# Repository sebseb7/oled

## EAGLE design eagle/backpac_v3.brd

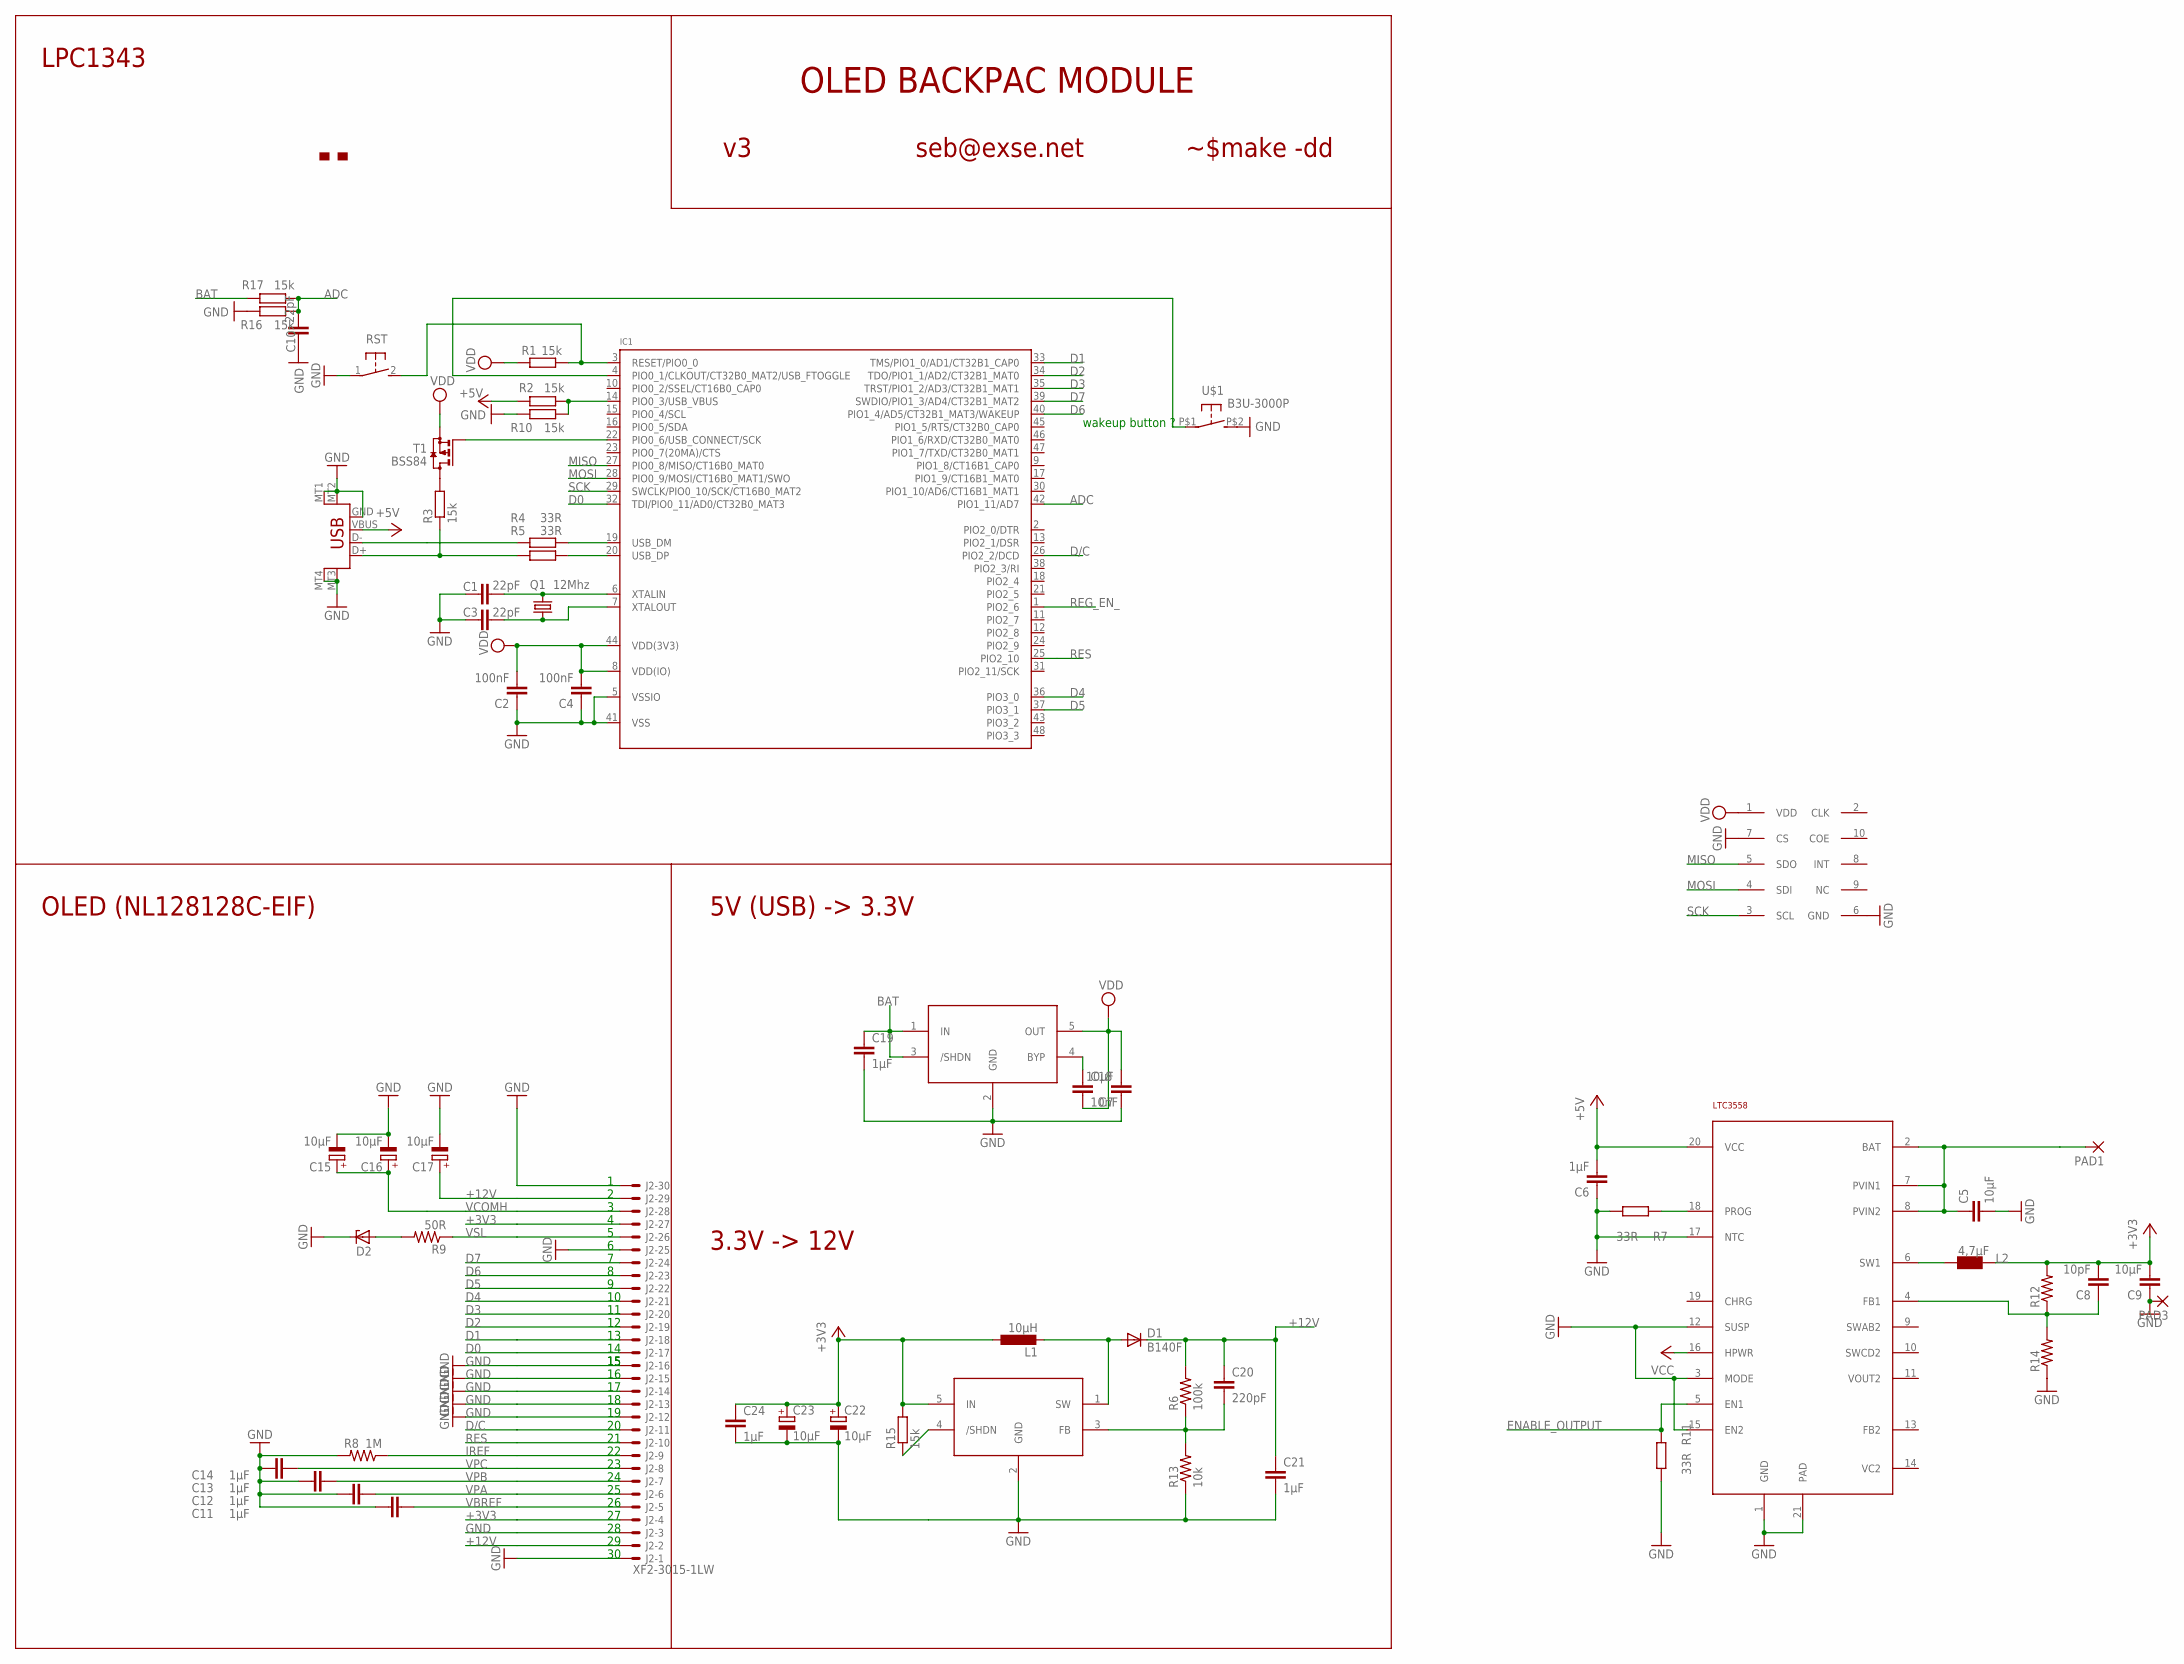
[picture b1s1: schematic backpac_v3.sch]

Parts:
C1, C3, C10: 22pF; C0402
C2, C4: 100nF; C0402
C5, C7, C9: 10µF; 0805
C6, C11, C12, C13, C14, C19, C21, C24: 1µF; 0805
C8: 10pF; 0805
C15, C16, C17, C22, C23: 10µF; SMC_A
C18: 10nF; 0402-CAP
C20: 220pF; 0805
D1: B140F; DO214AC
D2: ZENER-DIODESOT23; SOT23
IC1: LPC1343_QFP; LQFP48
IC2: LTC3558; UD-QFN20
IC3: LT1761; SOT23-5L
IC4: LM27313; SOT23-5L
IC5: RV-2123-C2
J2: XF2-3015-1LW; XF2H-3015-1LW
L1: 10µH; L1812
L2: 4,7µF; VLF4012A; PART VLF4012A
PAD1, PAD3: SMD2; SMD1,27-2,54
Q1: 12Mhz; MT
R1, R2, R3, R10, R15, R16, R17: 15k; R0402
R4, R5, R7, R11: 33R; R0402
R6: 100k; 0805
R8: 1M; 0805
R9: 50R; 0805
R12, R14: RESISTOR0805-RES; 0805
R13: 10k; 0805
RST: SWITCH_MCTAEF
T1: BSS84; SOT23
U$1: B3U-3000P
U$3: MAKE-DD_LOGO'REGULAR'; MAKE-DD_LOGO
X1: USB-MICROB

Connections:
+3V3: C8.2, C9.2, C22.+, C23.+, C24.1, IC4.5 (IN), J2.4 (MS), J2.27 (MS), L1.1, L2.P$4 (2), R12.2, R15.2
+5V: C6.2, IC2.20 (VCC), R2.2, X1.VBUS
+12V: C17.+, C20.1, C21.1, D1.C, J2.2 (MS), J2.29 (MS), R6.2
ADC: C10.2, IC1.42 (PIO1_11/AD7), R16.1, R17.1
BAT: C5.1, C19.1, IC2.2 (BAT), IC2.7 (PVIN1), IC2.8 (PVIN2), IC3.1 (IN), IC3.3 (/SHDN), PAD1.1, R17.2
D0: IC1.32 (TDI/PIO0_11/AD0/CT32B0_MAT3), J2.17 (MS)
D1: IC1.33 (TMS/PIO1_0/AD1/CT32B1_CAP0), J2.18 (MS)
D2: IC1.34 (TDO/PIO1_1/AD2/CT32B1_MAT0), J2.19 (MS)
D3: IC1.35 (TRST/PIO1_2/AD3/CT32B1_MAT1), J2.20 (MS)
D4: IC1.36 (PIO3_0), J2.21 (MS)
D5: IC1.37 (PIO3_1), J2.22 (MS)
D6: IC1.40 (PIO1_4/AD5/CT32B1_MAT3/WAKEUP), J2.23 (MS)
D7: IC1.39 (SWDIO/PIO1_3/AD4/CT32B1_MAT2), J2.24 (MS)
D/C: IC1.26 (PIO2_2/DCD), J2.11 (MS)
ENABLE_OUTPUT: IC2.5 (EN1), R11.2
GND: C1.1, C2.1, C3.1, C4.1, C5.2, C6.1, C7.1, C9.1, C10.1, C11.1, C12.1, C13.1, C14.1, C15.-, C16.-, C17.-, C19.2, C21.2, C22.-, C23.-, C24.2, D2.3 (C), IC1.5 (VSSIO), IC1.41 (VSS), IC2.1 (GND), IC2.3 (MODE), IC2.12 (SUSP), IC2.15 (EN2), IC2.17 (NTC), IC2.21 (PAD), IC3.2 (GND), IC4.2 (GND), IC5.6 (GND), IC5.7 (CS), J2.1 (MSV), J2.3 (MS), J2.12 (MS), J2.13 (MS), J2.14 (MS), J2.15 (MS), J2.16 (MS), J2.25 (MS), J2.30 (MS), PAD3.1, R7.1, R8.2, R10.2, R11.1, R13.1, R14.1, R16.2, RST.1, U$1.P$2 (2), X1.GND, X1.MT1 (GND), X1.MT2 (GND), X1.MT3 (GND), X1.MT4 (GND)
IREF: J2.9 (MS), R8.1
MISO: IC1.27 (PIO0_8/MISO/CT16B0_MAT0), IC5.5 (SDO)
MOSI: IC1.28 (PIO0_9/MOSI/CT16B0_MAT1/SWO), IC5.4 (SDI)
unnamed: IC2.18 (PROG), R7.2
unnamed: D2.1 (A), R9.2
unnamed: C3.2, IC1.7 (XTALOUT), Q1.1
unnamed: C1.2, IC1.6 (XTALIN), Q1.3 (2)
unnamed: D1.A, IC4.1 (SW), L1.2
unnamed: C20.2, IC4.3 (FB), R6.1, R13.2
unnamed: IC1.3 (RESET/PIO0_0), R1.1, RST.2
unnamed: R3.2, T1.3 (D)
unnamed: IC1.22 (PIO0_6/USB_CONNECT/SCK), T1.1 (G)
unnamed: R3.1, R5.2, X1.D+
unnamed: R4.2, X1.D-
unnamed: IC1.14 (PIO0_3/USB_VBUS), R2.1, R10.1
unnamed: C8.1, IC2.4 (FB1), R12.1, R14.2
unnamed: IC1.19 (USB_DM), R4.1
unnamed: IC2.6 (SW1), L2.P$3 (1)
unnamed: IC1.4 (PIO0_1/CLKOUT/CT32B0_MAT2/USB_FTOGGLE), U$1.P$1 (1)
unnamed: IC1.20 (USB_DP), R5.1
unnamed: C18.1, IC3.4 (BYP)
REG_EN_: IC1.1 (PIO2_6), IC4.4 (/SHDN), R15.1
RES: IC1.25 (PIO2_10), J2.10 (MS)
SCK: IC1.29 (SWCLK/PIO0_10/SCK/CT16B0_MAT2), IC5.3 (SCL)
VBREF: C11.2, J2.5 (MS)
VCC: IC2.16 (HPWR)
VCOMH: C15.+, C16.+, J2.28 (MS)
VDD: C2.2, C4.2, C7.2, C18.2, IC1.8 (VDD(IO)), IC1.44 (VDD(3V3)), IC3.5 (OUT), IC5.1 (VDD), R1.2, T1.2 (S)
VPA: C12.2, J2.6 (MS)
VPB: C13.2, J2.7 (MS)
VPC: C14.2, J2.8 (MS)
VSL: J2.26 (MS), R9.1

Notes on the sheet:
wakeup button ?
LPC1343
OLED (NL128128C-EIF)
5V (USB) -> 3.3V
3.3V -> 12V
seb@exse.net
OLED BACKPAC MODULE
~$make -dd

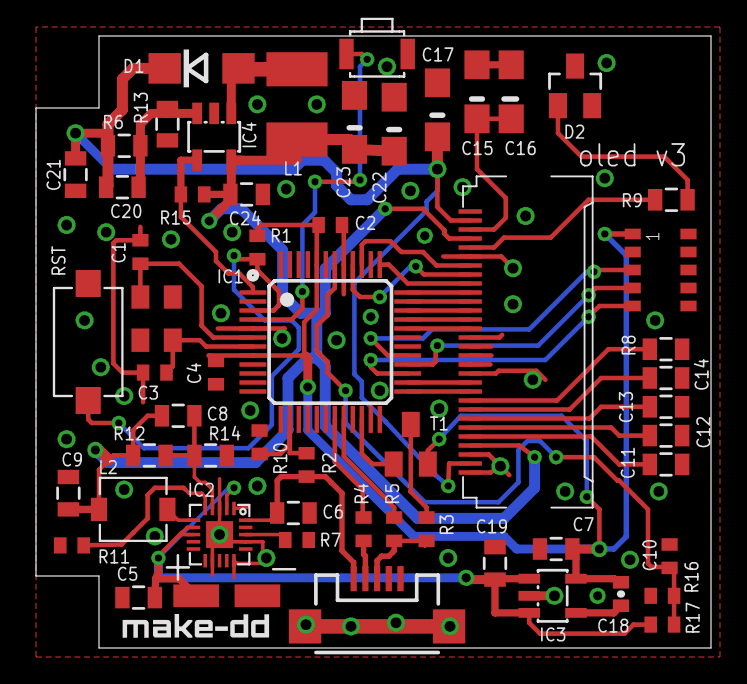
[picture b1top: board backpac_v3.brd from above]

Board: 2 copper layers, 37.5 x 34.0 mm, 59 parts (0 on the bottom side), 47 nets.

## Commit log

2012-03-16 init
2012-03-16 ignore
2012-03-24 misc
2012-03-29 added sdl simulator and some examples
2012-03-29 made it more irregular
2012-03-29 removed printf
2012-03-30 draw text
2012-03-30 text added
2012-03-30 red green fader
2012-04-03 added draw_number
2012-04-03 day cycle
2012-04-03 signed numbers
2012-04-03 cleanup
2012-04-07 minute ++ 3x
2012-04-07 minute++ 1x
2012-04-07 connector
2012-04-13 first working version
2012-04-13 optimized setled
2012-04-13 moved cicrle & added text
2012-04-13 tmp changes
2012-04-13 converted to 4wire and faster spi transfers
2012-04-14 minor stuff
2012-04-14 moved font into pgmspace and minor stuff
2012-04-15 usart
2012-04-16 version v1
2012-04-17 minor updates
2012-04-18 fix!
2012-04-20 ybxcmxby
2012-04-20 blue
2012-04-23 clang
2012-04-23 dither updates
2012-04-23 dither
2012-04-23 merge
2012-04-26 usb connect and vbus fix
2012-04-26 remapped the display pins better to the ports and fixed floating shutdown pin
2012-05-21 rerouted some wires
2012-05-21 removed test
2012-05-21 added arm code (not yet working
2012-05-21 reorg
2012-05-21 added images & cosmetic changes
2012-05-21 comments
2012-05-21 small changes
2012-05-21 ignoance
2012-05-25 backpac_b.sch
2012-05-25 new versions
2012-05-25 small fix
2012-05-26 new variants
2012-05-27 production run 2
2012-06-09 blahfasel
2012-06-09 redone
2012-06-09 format
2012-06-19 working
2012-06-19 diode
2012-06-19 missing files
2012-06-19 table fix
2012-06-19 debugging
2012-06-19 v3-pre
2012-06-19 final fix
2012-06-22 new colours
2012-06-26 compile warnings
2012-06-26 save colors & date
2012-06-26 rect & filled rect
2012-06-26 moved colors to separate file
2012-06-26 added segments animation
2012-06-26 moved commcode to animation
2012-06-26 buildfix
2012-06-26 dayline
2012-06-26 save
2012-06-26 half way
2012-06-26 comm
2012-06-26 fixes
2012-07-30 catia files of case
2012-09-26 osx fixes
2013-07-03 refinements
2013-07-03 refinement

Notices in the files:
parts and their libraries:
SparkFun-Capacitors: Licensing: CC v3.0 Share-Alike You are welcome to use this library for commercial purposes.
